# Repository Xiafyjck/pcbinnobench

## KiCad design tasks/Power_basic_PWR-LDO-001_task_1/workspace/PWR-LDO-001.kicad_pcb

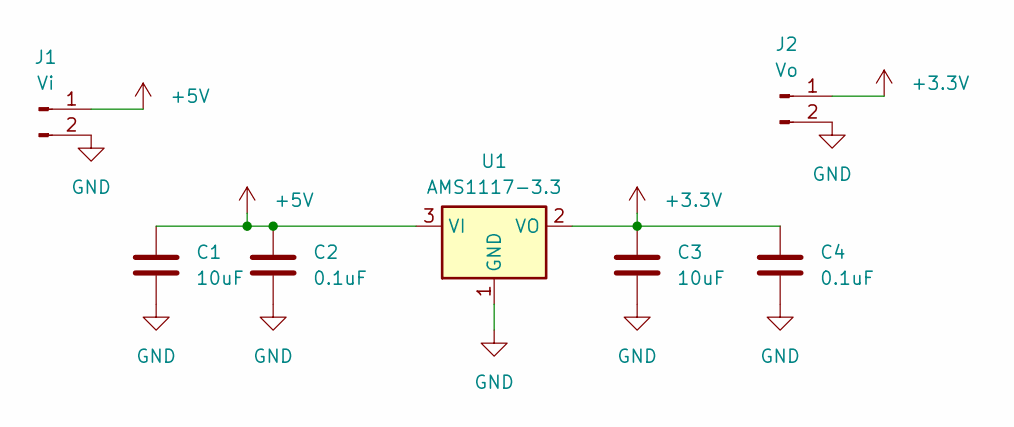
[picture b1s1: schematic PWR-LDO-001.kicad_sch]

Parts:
C1, C3: 10uF; C_0805_2012Metric
C2, C4: 0.1uF; C_0805_2012Metric
J1: Vi; JST_XH_B2B-XH-AM_1x02_P2.50mm_Vertical
J2: Vo; JST_XH_B2B-XH-AM_1x02_P2.50mm_Vertical
U1: AMS1117-3.3; SOT-223-3_TabPin2

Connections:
+3.3V: C3.1, C4.1, J2.1, U1.2 (VO)
+5V: C1.1, C2.1, J1.1, U1.3 (VI)
GND: C1.2, C2.2, C3.2, C4.2, J1.2, J2.2, U1.1 (GND)

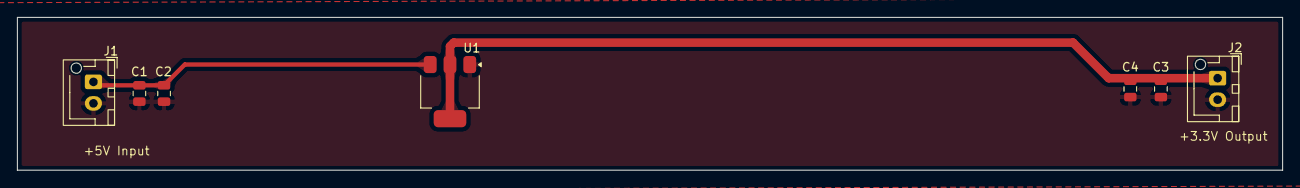
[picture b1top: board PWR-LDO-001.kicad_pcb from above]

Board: 2 copper layers, 147.2 x 17.8 mm, 7 parts (0 on the bottom side), 3 nets.

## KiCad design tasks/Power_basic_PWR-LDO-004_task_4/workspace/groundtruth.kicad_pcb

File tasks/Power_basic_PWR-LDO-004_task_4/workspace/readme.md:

This project aims to implement 12V to 5V using LDO.
Schematic part:
Use PTVS12VZ1USK and two 100uF electrolytic capacitors.
FB two resistor values derived from VOUT = 0.6 * R1 / R2.
PCB part:
Resistors close to FB pin.
12V, 5V trace widths as large as possible, added some return vias.

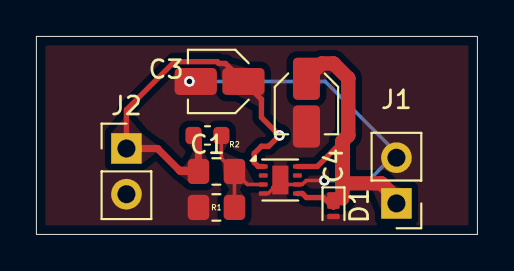
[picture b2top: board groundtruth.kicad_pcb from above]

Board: 2 copper layers, 24.5 x 11.0 mm, 9 parts (0 on the bottom side), 4 nets.

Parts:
C1, C4: 100UF; C_Elec_3x5.4
C3: 100NF; C_0603_1608Metric
D1: PTVS12VZ1USK; Nexperia_DSN1608-2_1.6x0.8mm
J1, J2: Conn_01x02_Pin; PinHeader_1x02_P2.54mm_Vertical
R1: 2000K; R_0805_2012Metric_Pad1.20x1.40mm_HandSolder
R2: 100K; R_0805_2012Metric_Pad1.20x1.40mm_HandSolder
U2: TLV76750QWDRBxQ1; WSON-8-1EP_2x2mm_P0.5mm_EP0.9x1.6mm

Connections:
+5V: C1.1, C3.1, J2.1, R1.2, U2.1 (OUT)
+12V: C4.1, D1.1 (K), J1.1, U2.5 (EN), U2.8 (IN)
GND: C1.2, C4.2, D1.2 (A), J1.2, J2.2, R2.1, U2.4 (GND), U2.6 (GND), U2.9 (PAD)
unnamed: C3.2, R1.1, R2.2, U2.3 (SNS)

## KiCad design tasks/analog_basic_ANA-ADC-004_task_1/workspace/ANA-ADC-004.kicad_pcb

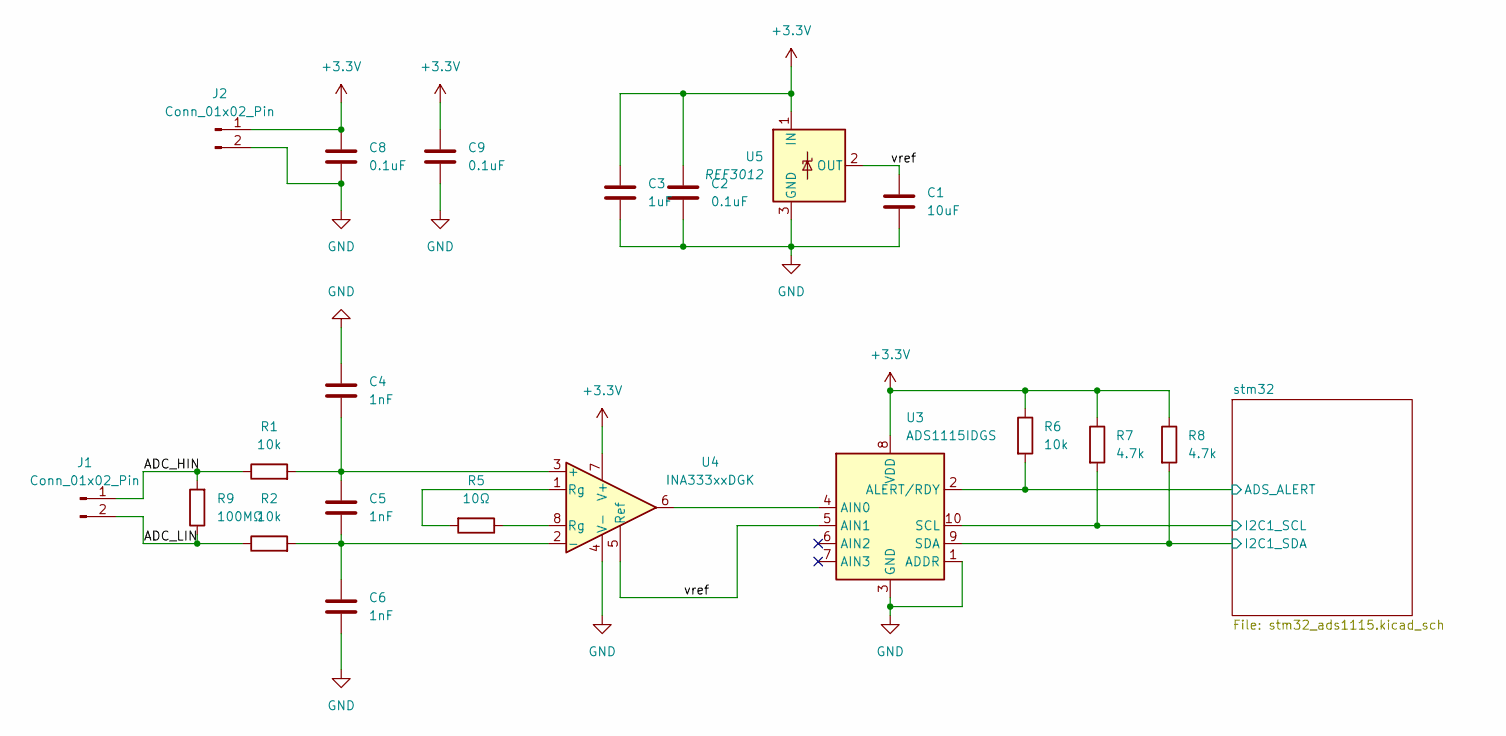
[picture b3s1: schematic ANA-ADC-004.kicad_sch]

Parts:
C1: 10uF; C_0805_2012Metric
C2, C8, C9: 0.1uF; C_0805_2012Metric
C3: 1uF; C_0805_2012Metric
C4, C5, C6: 1nF; C_0805_2012Metric
J1, J2: Conn_01x02_Pin; JST_XH_B2B-XH-AM_1x02_P2.50mm_Vertical
R1, R2, R6: 10k; R_0805_2012Metric
R5: 10Ω; R_0805_2012Metric
R7, R8: 4.7k; R_0805_2012Metric
R9: 100MΩ; R_2512_6332Metric
U3: ADS1115IDGS; TSSOP-10_3x3mm_P0.5mm
U4: INA333xxDGK; VSSOP-8_3x3mm_P0.65mm
U5: REF3012; SOT-23

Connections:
+3.3V: C2.1, C3.1, C8.1, C9.1, J2.1, R6.1, R7.1, R8.1, U3.8 (VDD), U4.7 (V+), U5.1 (IN); also elsewhere on the board
/ADC_HIN: J1.1, R1.1, R9.2
/ADC_LIN: J1.2, R2.1, R9.1
/stm32/ADS_ALERT: R6.2, U3.2 (ALERT/RDY); also elsewhere on the board
/stm32/I2C1_SCL: R7.2, U3.10 (SCL); also elsewhere on the board
/stm32/I2C1_SDA: R8.2, U3.9 (SDA); also elsewhere on the board
/vref: C1.1, U3.5 (AIN1), U4.5 (Ref), U5.2 (OUT)
GND: C1.2, C2.2, C3.2, C4.1, C6.2, C8.2, C9.2, J2.2, U3.1 (ADDR), U3.3 (GND), U4.4 (V-), U5.3 (GND); also elsewhere on the board
unnamed: R5.1, U4.8 (Rg)
unnamed: R5.2, U4.1 (Rg)
unnamed: U3.4 (AIN0), U4.6
unnamed: C4.2, C5.1, R1.2, U4.3 (+)
unnamed: C5.2, C6.1, R2.2, U4.2 (-)

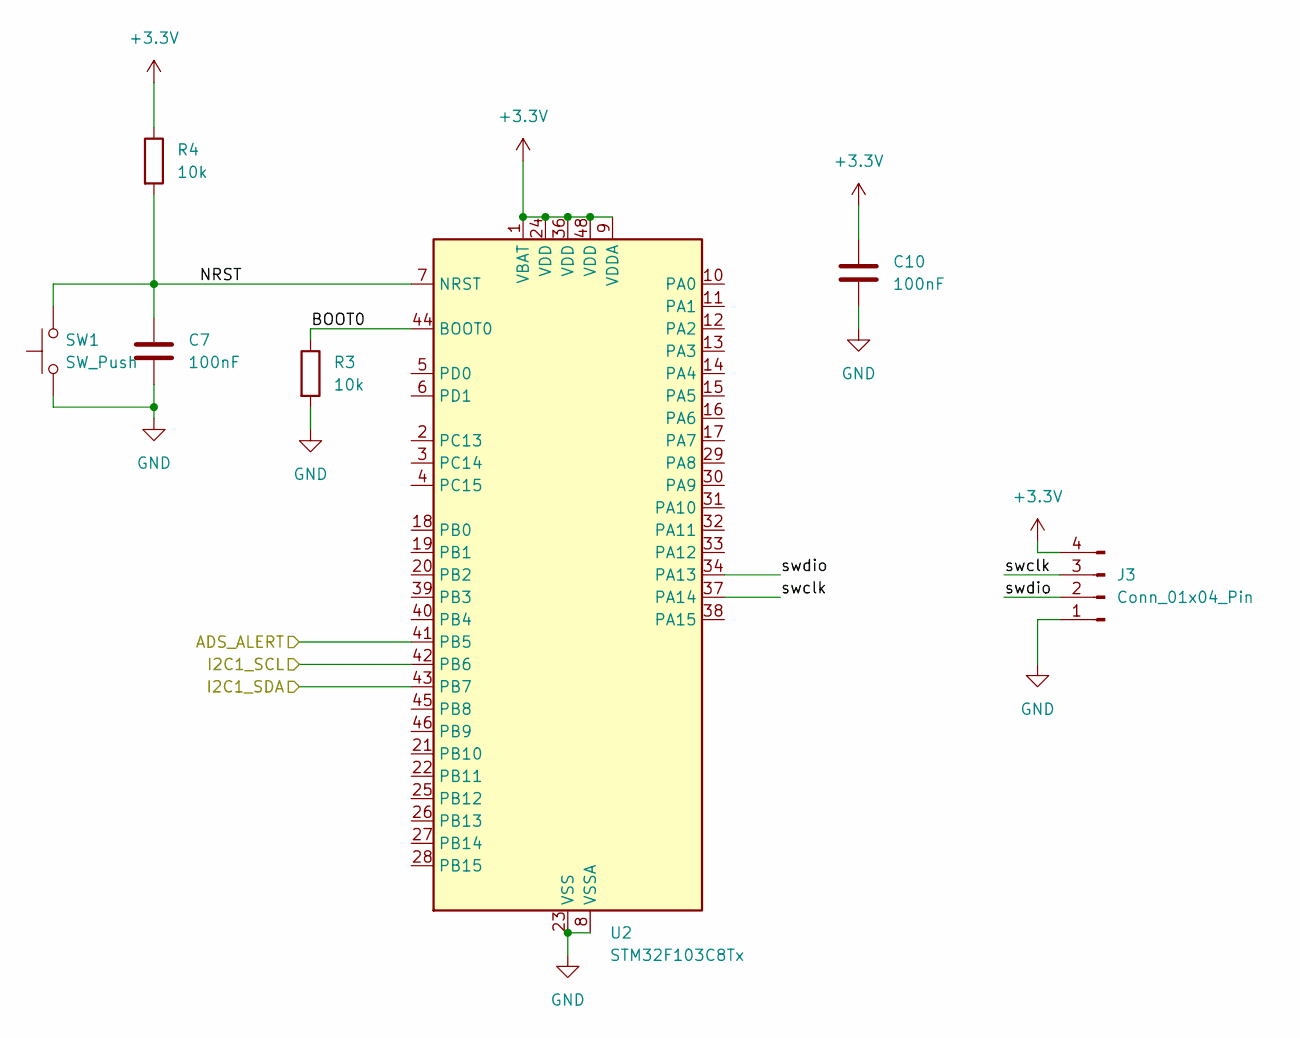
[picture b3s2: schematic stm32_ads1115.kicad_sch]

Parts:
C7, C10: 100nF; C_0805_2012Metric
J3: Conn_01x04_Pin; JST_XH_B4B-XH-AM_1x04_P2.50mm_Vertical
R3, R4: 10k; R_0805_2012Metric
SW1: SW_Push; SW_PUSH_6mm
U2: STM32F103C8Tx; LQFP-48_7x7mm_P0.5mm

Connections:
+3.3V: C10.1, J3.4, R4.1, U2.1 (VBAT), U2.9 (VDDA), U2.24 (VDD), U2.36 (VDD), U2.48 (VDD); also elsewhere on the board
/stm32/ADS_ALERT: U2.41 (PB5); also elsewhere on the board
/stm32/BOOT0: R3.1, U2.44 (BOOT0)
/stm32/I2C1_SCL: U2.42 (PB6); also elsewhere on the board
/stm32/I2C1_SDA: U2.43 (PB7); also elsewhere on the board
/stm32/NRST: C7.1, R4.2, SW1.2, U2.7 (NRST)
/stm32/swclk: J3.3, U2.37 (PA14)
/stm32/swdio: J3.2, U2.34 (PA13)
GND: C7.2, C10.2, J3.1, R3.2, SW1.1, U2.8 (VSSA), U2.23 (VSS), U2.35 (VSS), U2.47 (VSS); also elsewhere on the board

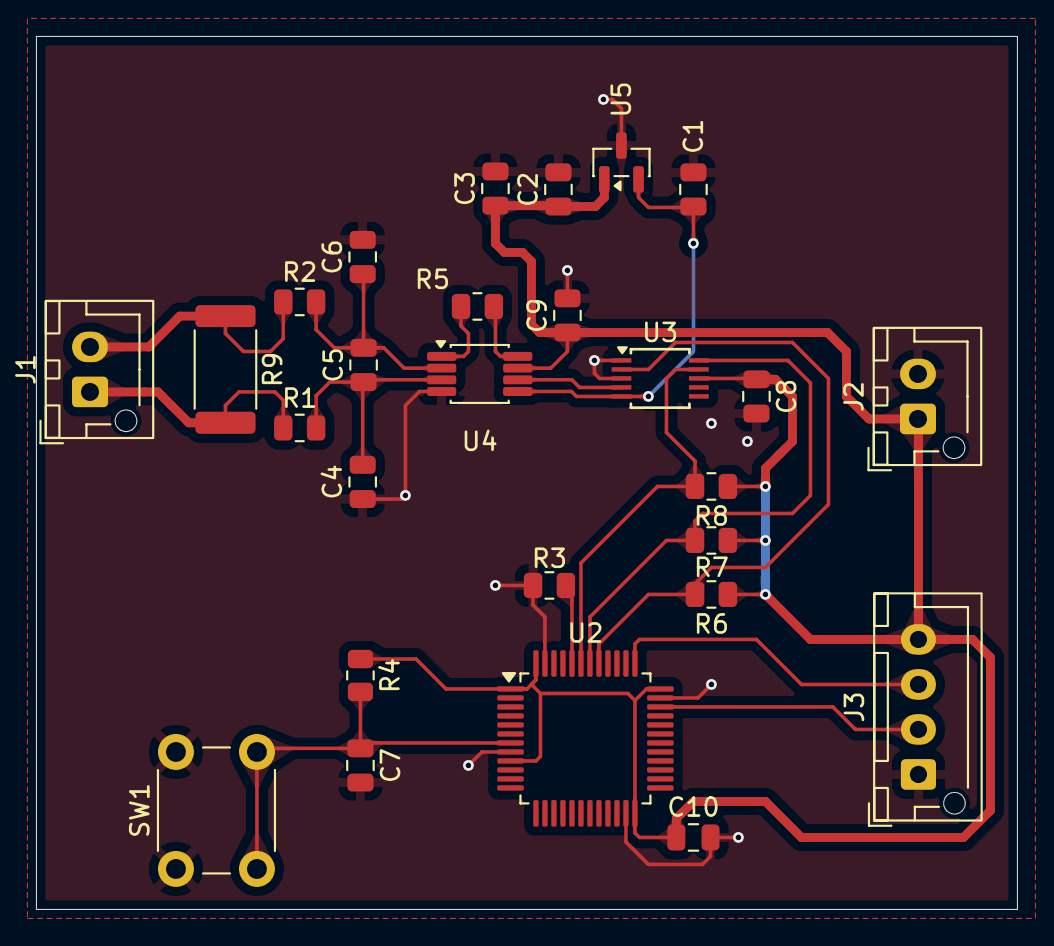
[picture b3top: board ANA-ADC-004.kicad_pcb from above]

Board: 2 copper layers, 54.5 x 48.5 mm, 27 parts (0 on the bottom side), 17 nets.

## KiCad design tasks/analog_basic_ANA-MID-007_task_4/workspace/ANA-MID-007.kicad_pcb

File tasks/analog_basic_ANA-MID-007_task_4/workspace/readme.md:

# Photodiode Transimpedance Amplifier Sampling Board

This directory contains KiCad reference project, datasheets, and fault localization tasks for the photodiode transimpedance amplifier sampling board.

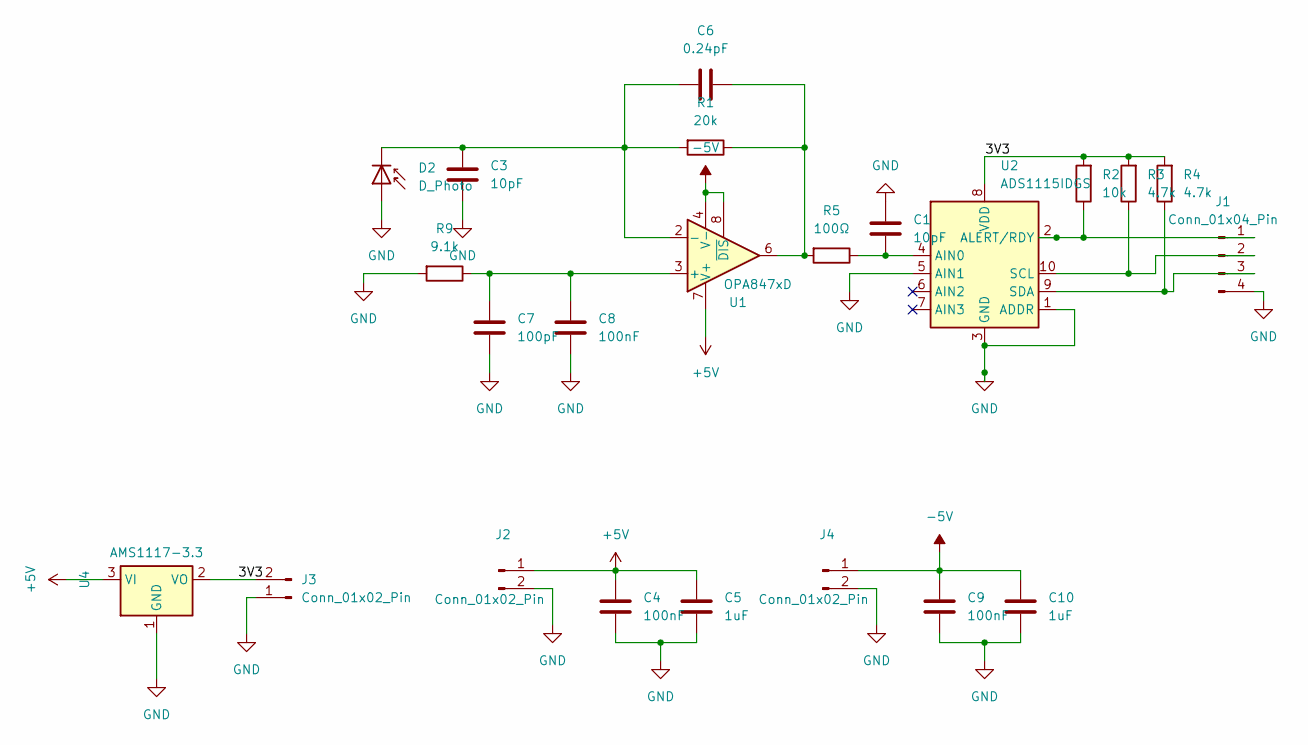
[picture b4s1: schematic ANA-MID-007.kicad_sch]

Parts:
C1, C3: 10pF; C_0805_2012Metric
C4, C8, C9: 100nF; C_0805_2012Metric
C5, C10: 1uF; C_0805_2012Metric
C6: 0.24pF; C_0805_2012Metric
C7: 100pF; C_0805_2012Metric
D2: D_Photo; TO-18-2
J1: Conn_01x04_Pin; PinHeader_1x04_P2.54mm_Horizontal
J2, J3, J4: Conn_01x02_Pin; PinHeader_1x02_P2.54mm_Horizontal
R1: 20k; R_0805_2012Metric
R2: 10k; R_0805_2012Metric
R3, R4: 4.7k; R_0805_2012Metric
R5: 100Ω; R_0805_2012Metric
R9: 9.1k; R_0805_2012Metric
U1: OPA847xD; SOIC-8_3.9x4.9mm_P1.27mm
U2: ADS1115IDGS; TSSOP-10_3x3mm_P0.5mm
U4: AMS1117-3.3; SOT-223-3_TabPin2

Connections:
+5V: C4.1, C5.1, J2.1, U1.7 (V+), U4.3 (VI); also elsewhere on the board
-5V: C9.1, C10.1, J4.1, U1.4 (V-), U1.8 (~DIS)
/3V3: J3.2, R2.2, R3.2, R4.2, U2.8 (VDD), U4.2 (VO); also elsewhere on the board
GND: C1.2, C3.2, C4.2, C5.2, C7.2, C8.2, C9.2, C10.2, D2.2 (A), J1.4, J2.2, J3.1, J4.2, R9.2, U2.1 (ADDR), U2.3 (GND), U2.5 (AIN1), U4.1 (GND); also elsewhere on the board
unnamed: C6.2, R1.1, R5.2, U1.6
unnamed: C3.1, C6.1, D2.1 (K), R1.2, U1.2 (-)
unnamed: J1.1, R2.1, U2.2 (ALERT/RDY)
unnamed: J1.2, R3.1, U2.10 (SCL)
unnamed: J1.3, R4.1, U2.9 (SDA)
unnamed: C7.1, C8.1, R9.1, U1.3 (+)
unnamed: C1.1, R5.1, U2.4 (AIN0)

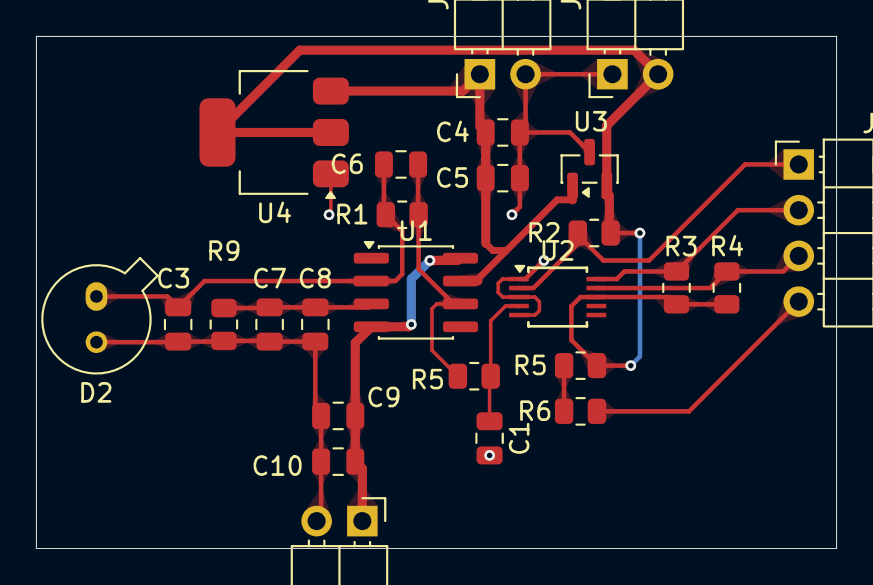
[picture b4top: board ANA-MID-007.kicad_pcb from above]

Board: 2 copper layers, 44.5 x 28.4 mm, 26 parts (0 on the bottom side), 12 nets.

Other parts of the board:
R5#2, R6: 10k; R_0805_2012Metric
U3: REF3033; SOT-23

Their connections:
+5V: U3.1 (IN); also elsewhere on the board
/3V3: R5#2.2, U3.2 (OUT); also elsewhere on the board
GND: R6.1, U3.3 (GND); also elsewhere on the board
unnamed: R5#2.1, R6.2

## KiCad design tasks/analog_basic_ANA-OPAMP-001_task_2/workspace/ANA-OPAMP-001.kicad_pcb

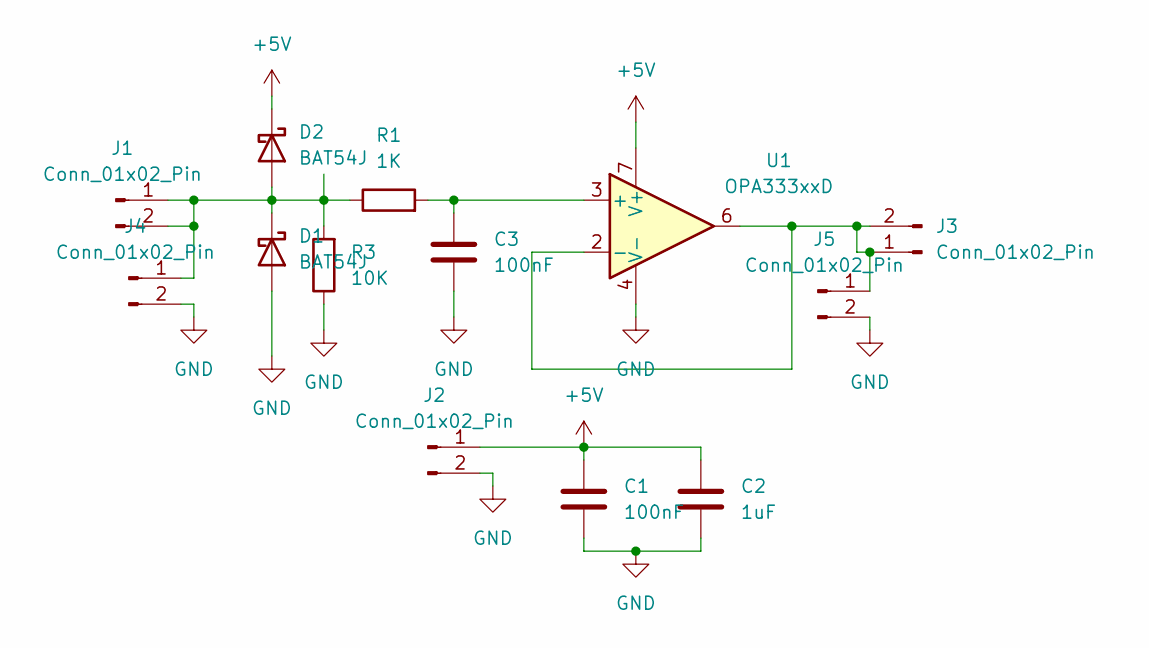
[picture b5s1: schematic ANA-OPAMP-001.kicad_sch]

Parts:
C1, C3: 100nF; C_0805_2012Metric
C2: 1uF; C_0805_2012Metric
D1, D2: BAT54J; D_SOD-323F
J1, J2, J3: Conn_01x02_Pin; PinHeader_1x02_P2.54mm_Horizontal
J4, J5: Conn_01x02_Pin; SMA_Amphenol_132289_EdgeMount
R1: 1K; R_0805_2012Metric
R3: 10K; R_0805_2012Metric
U1: OPA333xxD; SOIC-8_3.9x4.9mm_P1.27mm

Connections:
+5V: C1.1, C2.1, D2.1 (K), J2.1, U1.7 (V+)
GND: C1.2, C2.2, C3.2, D1.2 (A), J2.2, J4.2, J5.2, R3.1, U1.4 (V-)
unnamed: D1.1 (K), D2.2 (A), J1.1, J1.2, J4.1, R1.1, R3.2
unnamed: J3.1, J3.2, J5.1, U1.2 (-), U1.6
unnamed: C3.1, R1.2, U1.3 (+)

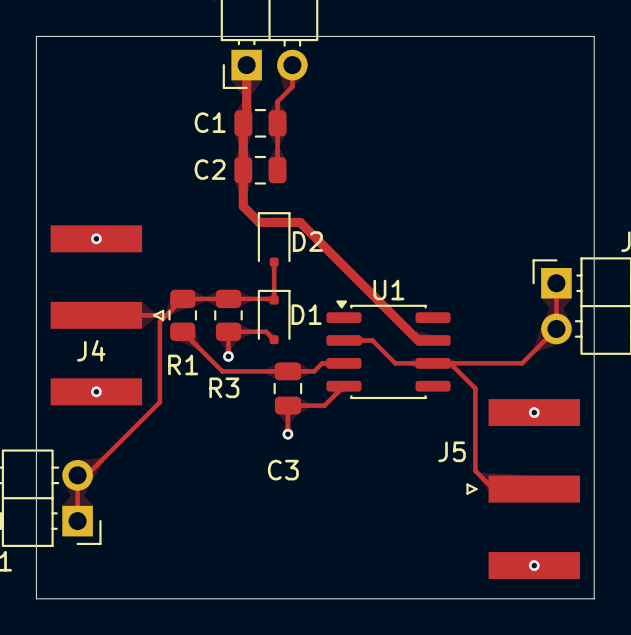
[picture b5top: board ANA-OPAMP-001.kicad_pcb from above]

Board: 2 copper layers, 31.0 x 31.2 mm, 13 parts (0 on the bottom side), 5 nets.

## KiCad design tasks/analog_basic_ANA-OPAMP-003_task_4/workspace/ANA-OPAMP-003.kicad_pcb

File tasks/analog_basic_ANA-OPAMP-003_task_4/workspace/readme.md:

OPA333 as inverting amplifier, AC coupled with bias, powered by XH254. Input and output signals selectable via SMA or XH254. Includes input signal filtering and power filtering.

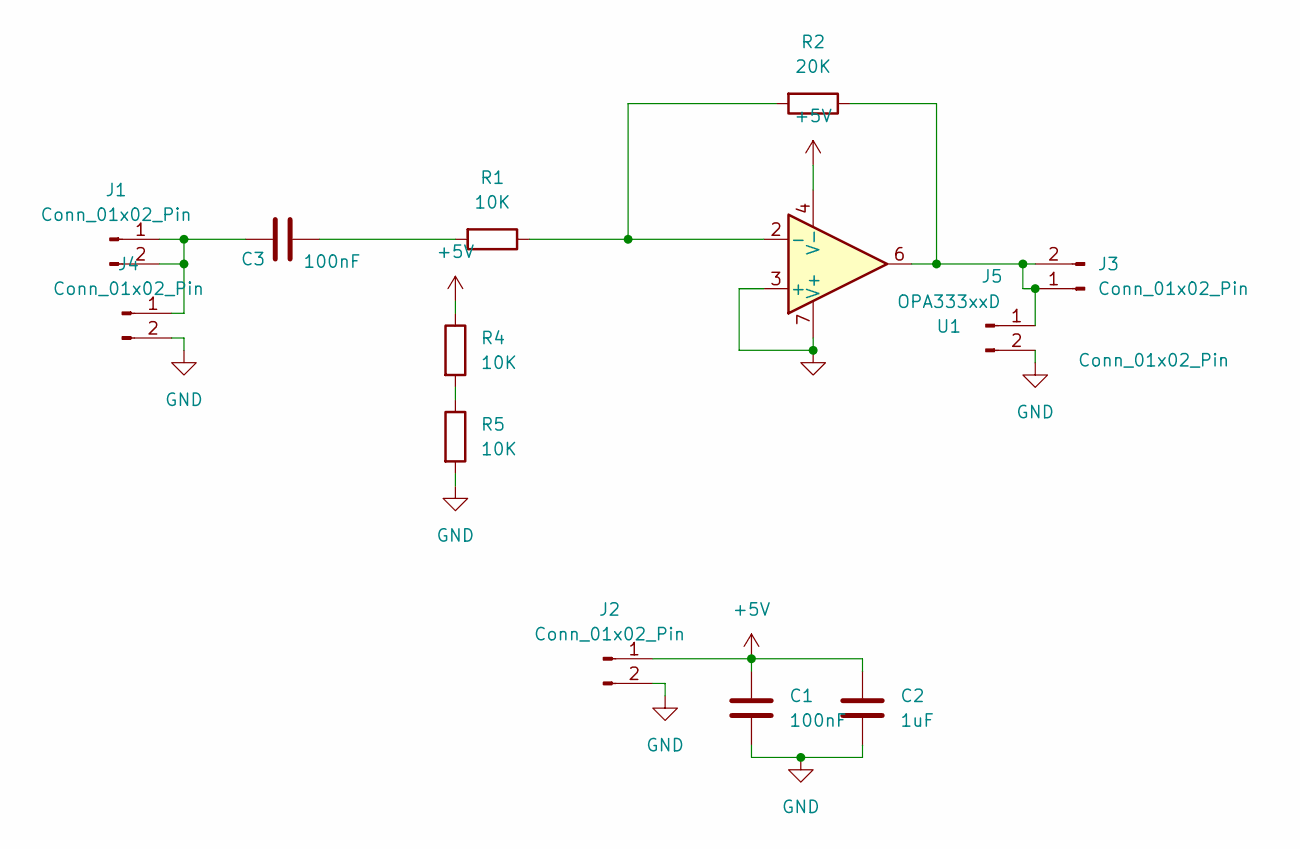
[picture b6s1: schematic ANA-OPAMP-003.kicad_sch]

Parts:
C1, C3: 100nF; C_0805_2012Metric
C2: 1uF; C_0805_2012Metric
J1, J2, J3: Conn_01x02_Pin; PinHeader_1x02_P2.54mm_Horizontal
J4, J5: Conn_01x02_Pin; SMA_Amphenol_132289_EdgeMount
R1, R4, R5: 10K; R_0805_2012Metric
R2: 20K; R_0805_2012Metric
U1: OPA333xxD; SOIC-8_3.9x4.9mm_P1.27mm

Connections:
+5V: C1.1, C2.1, J2.1, R4.1, U1.4 (V-)
GND: C1.2, C2.2, J2.2, J4.2, J5.2, R5.2, U1.3 (+), U1.7 (V+)
unnamed: C3.2, R1.2
unnamed: C3.1, J1.1, J1.2, J4.1
unnamed: J3.1, J3.2, J5.1, R2.1, U1.6
unnamed: R4.2, R5.1
unnamed: R1.1, R2.2, U1.2 (-)

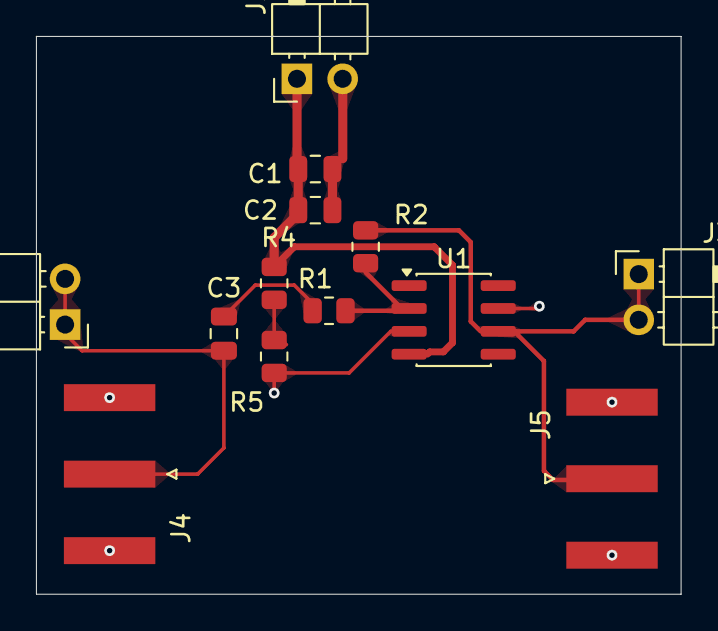
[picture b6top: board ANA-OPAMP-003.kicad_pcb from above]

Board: 2 copper layers, 35.8 x 31.0 mm, 13 parts (0 on the bottom side), 7 nets.

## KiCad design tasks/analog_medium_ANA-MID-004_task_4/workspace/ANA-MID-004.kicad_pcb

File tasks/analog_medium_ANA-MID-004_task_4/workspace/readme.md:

# 4-20mA Current Loop Sampling Board

This directory contains KiCad reference project, datasheets, and fault localization tasks for the 4-20mA current loop sampling board.

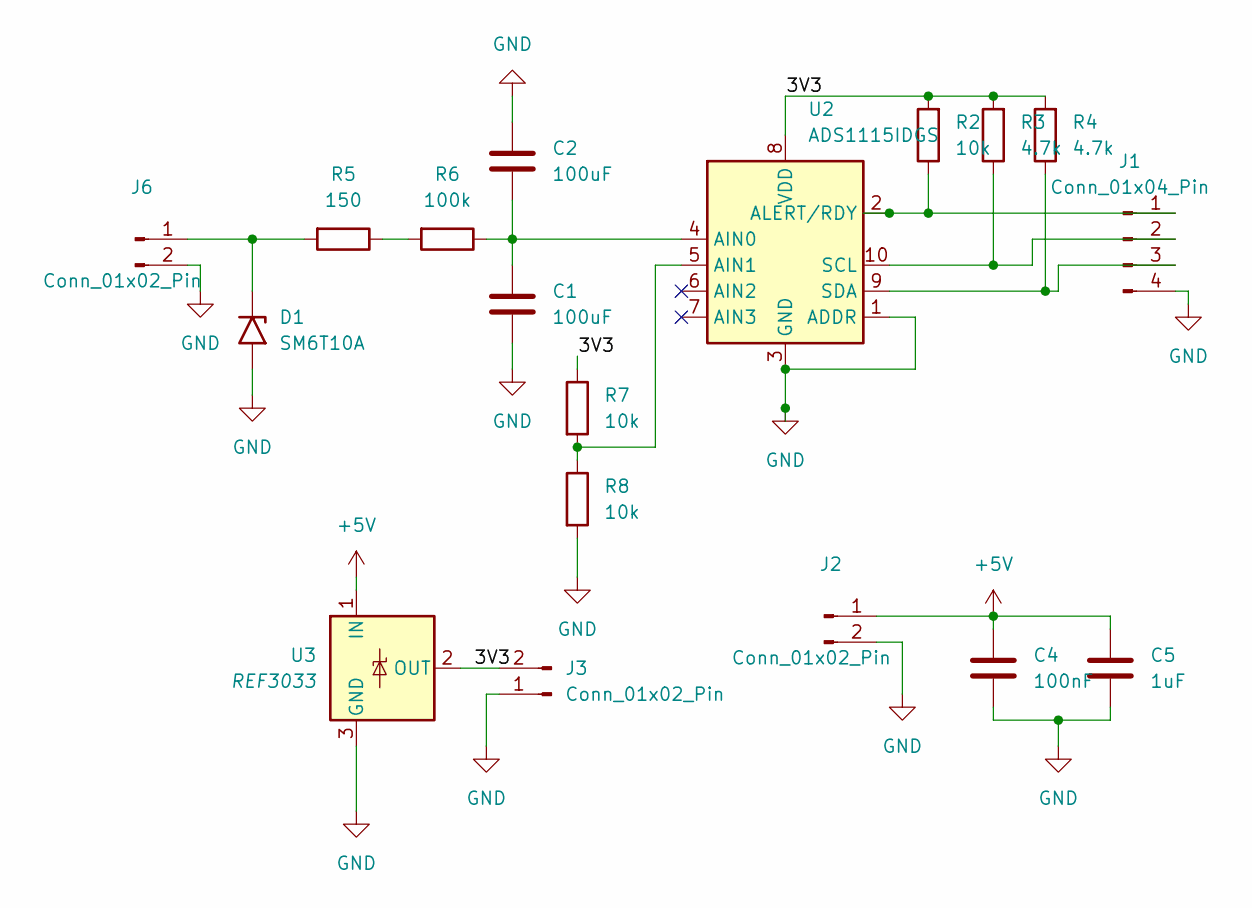
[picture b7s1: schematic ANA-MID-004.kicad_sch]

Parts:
C1, C2: 100uF; C_0805_2012Metric
C4: 100nF; C_0805_2012Metric
C5: 1uF; C_0805_2012Metric
D1: SM6T10A; D_SMB
J1: Conn_01x04_Pin; PinHeader_1x04_P2.54mm_Horizontal
J2, J3, J6: Conn_01x02_Pin; PinHeader_1x02_P2.54mm_Horizontal
R2, R7, R8: 10k; R_0805_2012Metric
R3, R4: 4.7k; R_0805_2012Metric
R5: 150; R_1206_3216Metric
R6: 100k; R_0805_2012Metric
U2: ADS1115IDGS; TSSOP-10_3x3mm_P0.5mm
U3: REF3033; SOT-23

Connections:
+5V: C4.1, C5.1, J2.1, U3.1 (IN)
/3V3: J3.2, R2.2, R3.2, R4.2, R7.1, U2.8 (VDD), U3.2 (OUT)
GND: C1.2, C2.1, C4.2, C5.2, D1.2 (A2), J1.4, J2.2, J3.1, J6.2, R8.2, U2.1 (ADDR), U2.3 (GND), U3.3 (GND)
unnamed: D1.1 (A1), J6.1, R5.2
unnamed: J1.1, R2.1, U2.2 (ALERT/RDY)
unnamed: J1.2, R3.1, U2.10 (SCL)
unnamed: J1.3, R4.1, U2.9 (SDA)
unnamed: R5.1, R6.2
unnamed: C1.1, C2.2, R6.1, U2.4 (AIN0)
unnamed: R7.2, R8.1, U2.5 (AIN1)

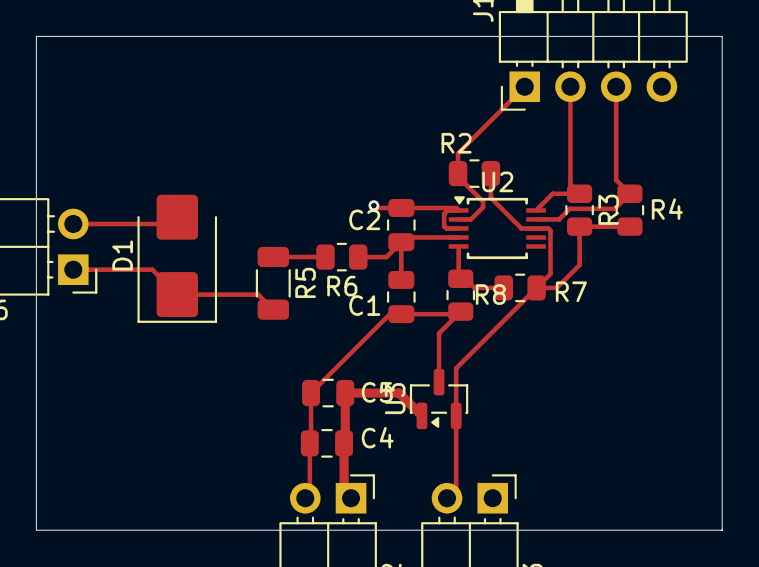
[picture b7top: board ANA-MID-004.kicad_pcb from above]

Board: 2 copper layers, 38.1 x 27.4 mm, 18 parts (0 on the bottom side), 10 nets.
